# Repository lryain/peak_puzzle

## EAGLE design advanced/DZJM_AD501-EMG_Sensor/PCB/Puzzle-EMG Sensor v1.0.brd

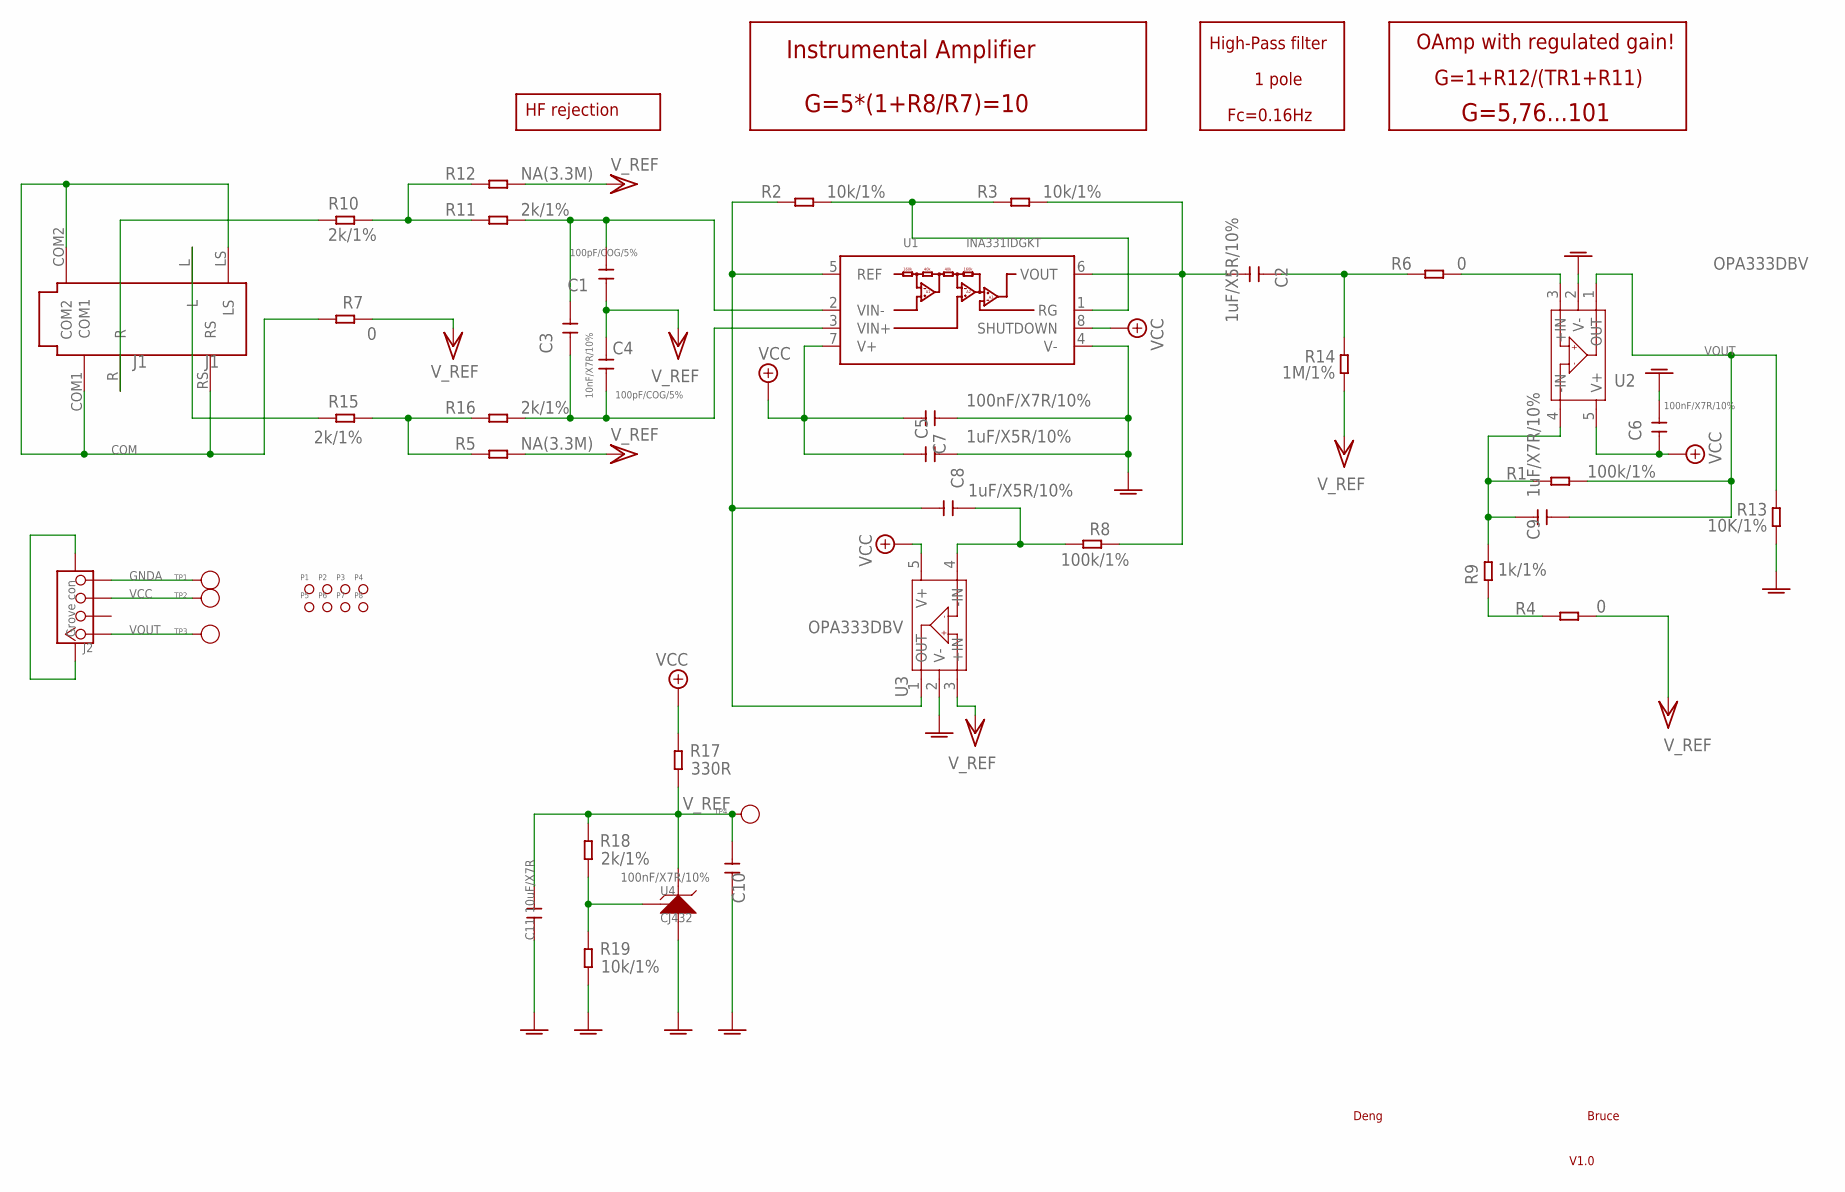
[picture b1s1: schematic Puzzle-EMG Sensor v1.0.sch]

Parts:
C1, C4: 100pF/COG/5%; C0603
C2, C7, C8: 1uF/X5R/10%; C0603
C3: 10nF/X7R/10%; C0603
C5, C6, C10: 100nF/X7R/10%; C0603
C9: 1uF/X7R/10%; C0603
C11: 10uF/X7R; C0805
J1: J1; 6P-SMD-3.5-NEW
J2: Grove con; 4P-SMD-2.0
P1, P2, P3, P4, P5, P6, P7, P8: PAD-MARK; ROUND-MARK-1.0
R1, R8: 100k/1%; R0603
R2, R3, R19: 10k/1%; R0603
R4, R6, R7: 0; R0603
R5, R12: NA(3.3M); R0603
R9: 1k/1%; R0603
R10, R11, R15, R16, R18: 2k/1%; R0603
R13: 10K/1%; R0603
R14: 1M/1%; R0603
R17: 330R; R0603
TP1: TP1; TP_4545
TP2: TP2; TP_4545
TP3: TP3; TP_4545
TP4: TP4; TP_4545
U1: INA331IDGKT; MSOP-8
U2, U3: OPA333DBV; SOT23-5
U4: CJ432; SOT23

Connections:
COM: J1.COM1, J1.COM2, J1.LS, J1.RS, R7.1
GNDA: C5.2, C6.1, C7.2, C10.2, C11.1, J2.4, R13.2, R19.1, TP1.T, U1.4 (V-), U2.2 (V-), U3.2 (V-), U4.3 (A)
unnamed: R4.1, R9.2
unnamed: C8.1, R8.1, U3.4 (-IN)
unnamed: J1.R, R10.1
unnamed: J1.L, R15.1
unnamed: R10.2, R11.2, R12.2
unnamed: R5.2, R15.2, R16.2
unnamed: C8.2, R2.2, U1.5 (REF), U3.1 (OUT)
unnamed: R2.1, R3.2, U1.1 (RG)
unnamed: C2.2, R6.2, R14.1
unnamed: R18.1, R19.2, U4.1 (R)
unnamed: C2.1, R3.1, R8.2, U1.6 (VOUT)
unnamed: C3.1, C4.1, R16.1, U1.3 (VIN+)
unnamed: C1.2, C3.2, R11.1, U1.2 (VIN-)
unnamed: R6.1, U2.3 (+IN)
unnamed: C9.1, R1.1, R9.1, U2.4 (-IN)
VCC: C5.1, C6.2, C7.1, J2.3, R17.2, TP2.T, U1.7 (V+), U1.8 (SHUTDOWN), U2.5 (V+), U3.5 (V+)
VOUT: C9.2, J2.1, R1.2, R13.1, TP3.T, U2.1 (OUT)
V_REF: C1.1, C4.2, C10.1, C11.2, J2.SS1, J2.SS2, R4.2, R5.1, R7.2, R12.1, R14.2, R17.1, R18.2, TP4.T, U3.3 (+IN), U4.2 (K)

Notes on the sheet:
G=1+R12/(TR1+R11)
G=5,76...101
Fc=0.16Hz
HF rejection
High-Pass filter
OAmp with regulated gain!
1 pole
G=5*(1+R8/R7)=10
Instrumental Amplifier
Deng
Bruce
V1.0

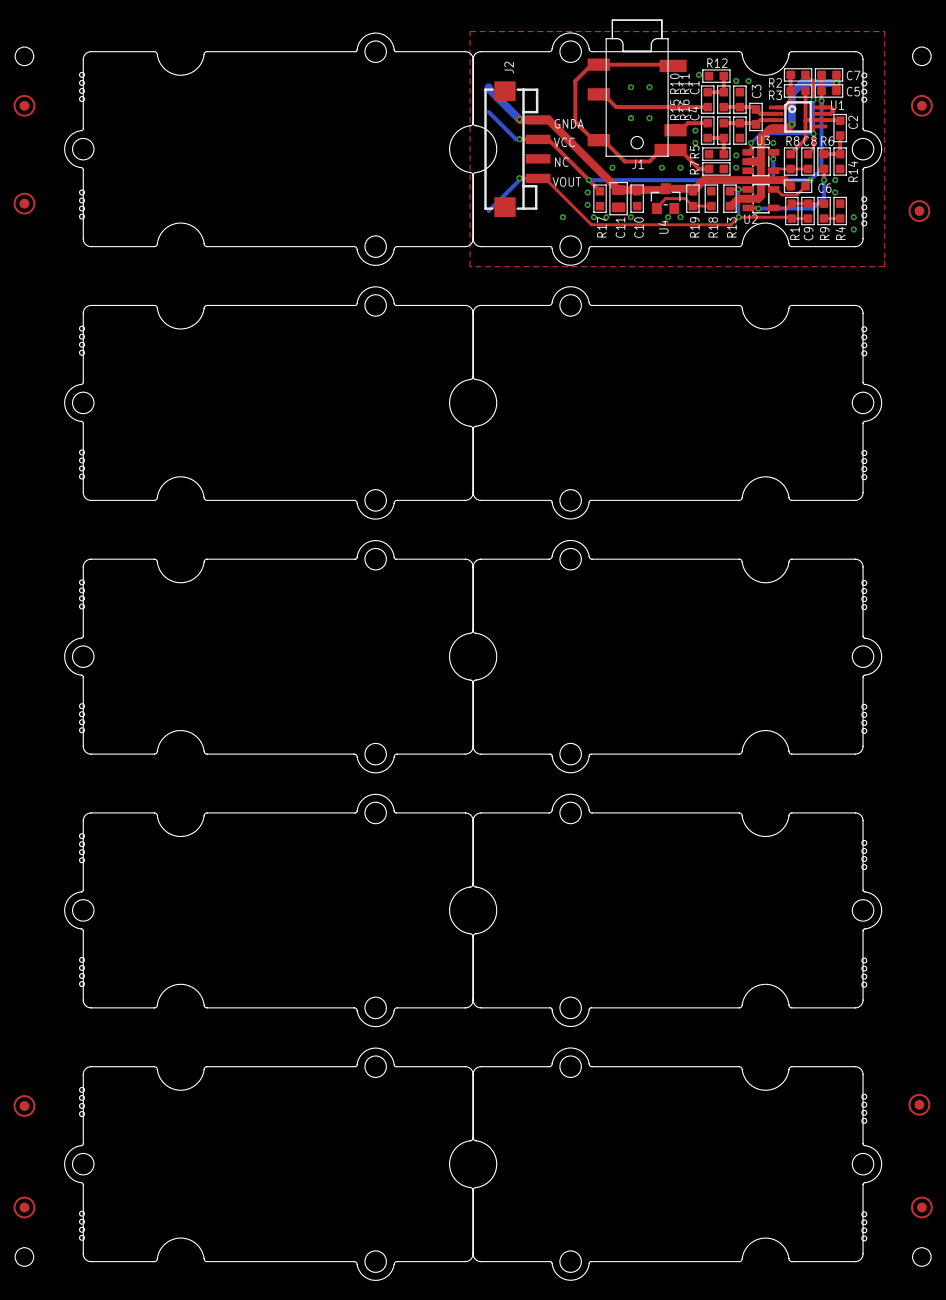
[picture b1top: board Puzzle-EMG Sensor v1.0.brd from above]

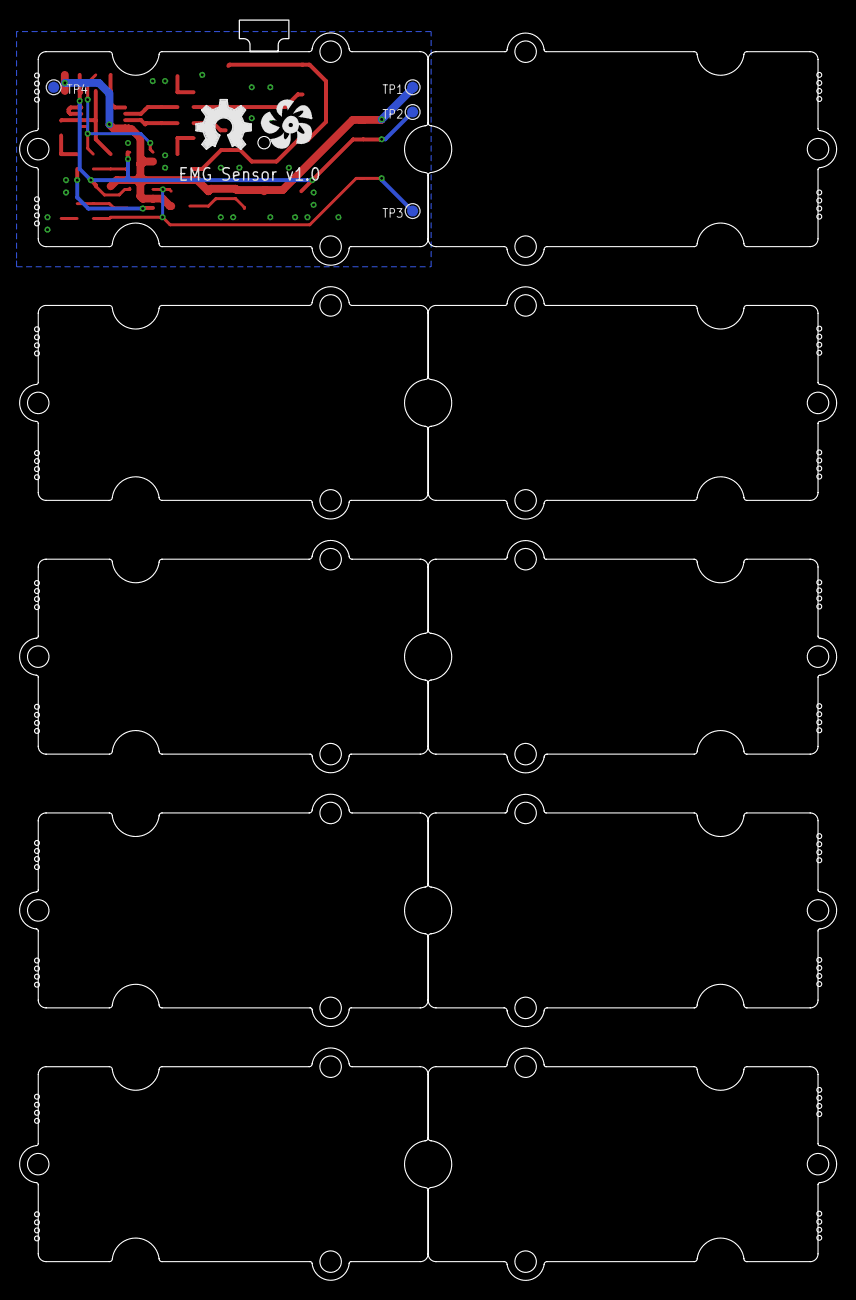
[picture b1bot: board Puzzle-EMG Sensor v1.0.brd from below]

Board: 2 copper layers, 83.7 x 129.3 mm, 60 parts (6 on the bottom side), 20 nets.

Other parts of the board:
U$2, U$5, U$6, U$7, U$8, U$9, U$10, U$11, U$12, U$13: GROVE-TEST-PLATFORM
U$3: OSHW_FILLX200_NOTEXT
U$14: DUINOFUN-LOGO-PCB-0.7

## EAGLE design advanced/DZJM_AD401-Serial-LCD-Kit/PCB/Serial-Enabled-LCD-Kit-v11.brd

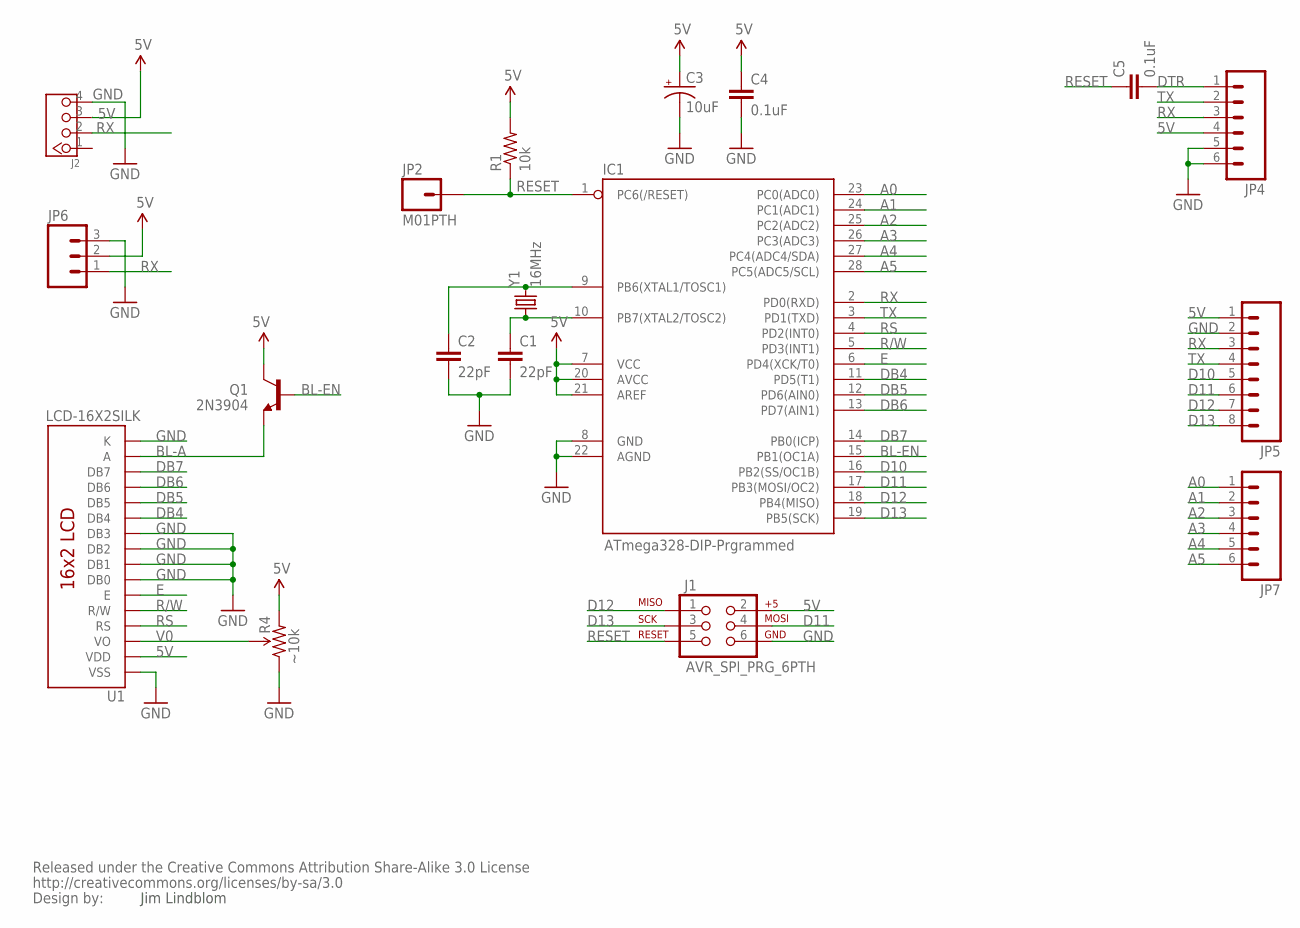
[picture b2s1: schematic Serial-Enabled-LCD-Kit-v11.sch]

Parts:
C1, C2: 22pF; CAP-PTH-SMALL2
C3: 10uF; CPOL-RADIAL-10UF-25V
C4, C5: 0.1uF; CAP-PTH-SMALL2
IC1: ATmega328-DIP-Prgrammed; DIL28-3
J1: AVR_SPI_PRG_6PTH; 2X3
J2: TWIG-4P-2.0'90D'; 4P-2.0-90D
JP2: M01PTH; 1X01
JP4, JP7: M06SIP; 1X06
JP5: M08; 1X08
JP6: M03PTH; 1X03
Q1: 2N3904; TO-92
R1: 10k; AXIAL-0.3
R4: ~10k; TRIM_POT_PTH
U1: LCD-16X2SILK; LCD-16X2
U$4: CREATIVE_COMMONS
Y1: 16MHz; HC49US

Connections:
5V: C3.1 (+), C4.1, IC1.7 (VCC), IC1.20 (AVCC), IC1.21 (AREF), J1.2, J2.3, JP4.4, JP5.1, JP6.2, Q1.3 (C), R1.P$2 (2), R4.3 (CW), U1.2 (VDD)
A0: IC1.23 (PC0(ADC0)), JP7.1
A1: IC1.24 (PC1(ADC1)), JP7.2
A2: IC1.25 (PC2(ADC2)), JP7.3
A3: IC1.26 (PC3(ADC3)), JP7.4
A4: IC1.27 (PC4(ADC4/SDA)), JP7.5
A5: IC1.28 (PC5(ADC5/SCL)), JP7.6
BL-A: Q1.1 (E), U1.15 (A)
BL-EN: IC1.15 (PB1(OC1A)), Q1.2 (B)
D10: IC1.16 (PB2(SS/OC1B)), JP5.5
D11: IC1.17 (PB3(MOSI/OC2)), J1.4, JP5.6
D12: IC1.18 (PB4(MISO)), J1.1, JP5.7
D13: IC1.19 (PB5(SCK)), J1.3, JP5.8
DB4: IC1.11 (PD5(T1)), U1.11 (DB4)
DB5: IC1.12 (PD6(AIN0)), U1.12 (DB5)
DB6: IC1.13 (PD7(AIN1)), U1.13 (DB6)
DB7: IC1.14 (PB0(ICP)), U1.14 (DB7)
DTR: C5.2, JP4.1
E: IC1.6 (PD4(XCK/T0)), U1.6 (E)
GND: C1.2, C2.2, C3.2 (-), C4.2, IC1.8 (GND), IC1.22 (AGND), J1.6, J2.4, JP4.5, JP4.6, JP5.2, JP6.3, R4.1 (CCW), U1.1 (VSS), U1.7 (DB0), U1.8 (DB1), U1.9 (DB2), U1.10 (DB3), U1.16 (K)
R/W: IC1.5 (PD3(INT1)), U1.5 (R/W)
RESET: C5.1, IC1.1 (PC6(/RESET)), J1.5, JP2.1, R1.P$1 (1)
RS: IC1.4 (PD2(INT0)), U1.4 (RS)
RX: IC1.2 (PD0(RXD)), J2.2, JP4.3, JP5.3, JP6.1
TX: IC1.3 (PD1(TXD)), JP4.2, JP5.4
V0: R4.2 (WIPER), U1.3 (VO)
XTAL1: C2.1, IC1.9 (PB6(XTAL1/TOSC1)), Y1.2
XTAL2: C1.1, IC1.10 (PB7(XTAL2/TOSC2)), Y1.1

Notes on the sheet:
Jim Lindblom

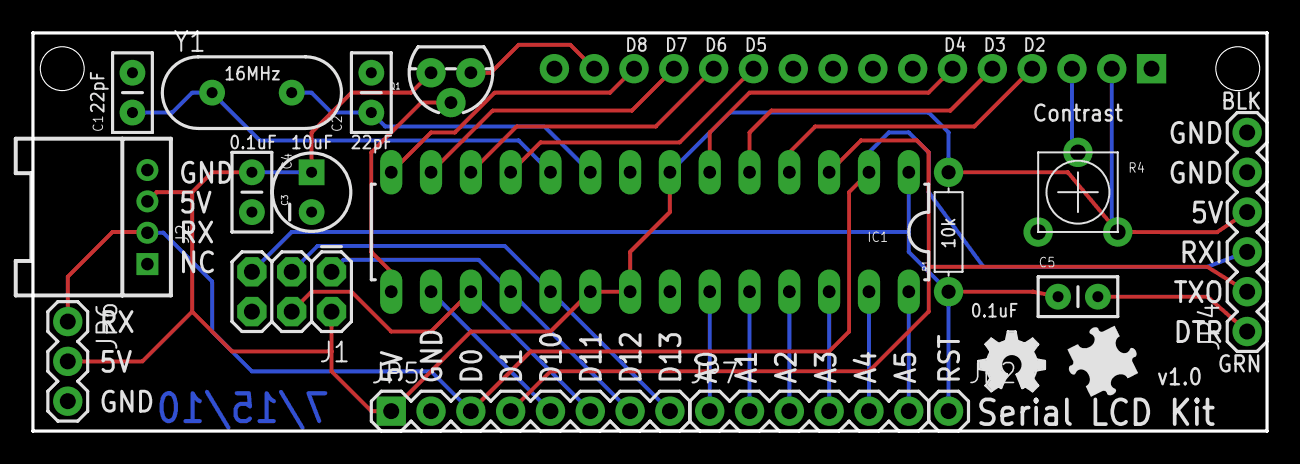
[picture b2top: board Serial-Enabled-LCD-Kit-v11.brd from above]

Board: 2 copper layers, 78.7 x 25.4 mm, 21 parts (1 on the bottom side), 28 nets.

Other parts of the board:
U$10: BRICK-LOGO-MIL-0.5
U$11: OPHW-LOGO-FILL-150

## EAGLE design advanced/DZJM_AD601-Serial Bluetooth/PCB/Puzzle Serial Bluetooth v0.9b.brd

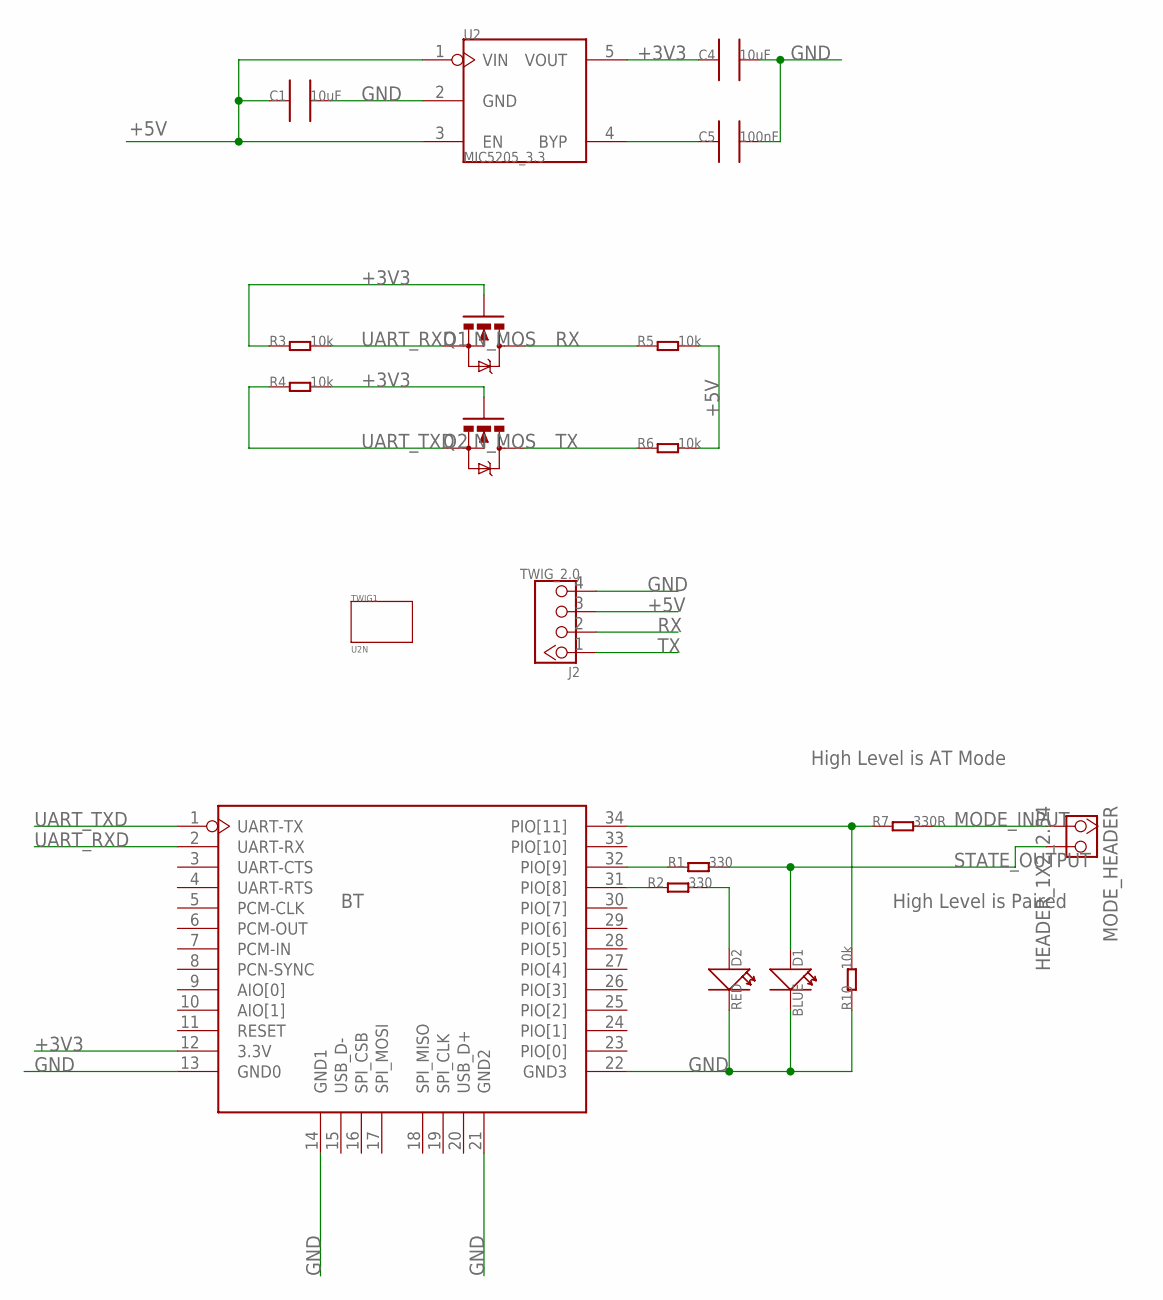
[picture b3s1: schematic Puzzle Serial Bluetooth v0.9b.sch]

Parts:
BT: SERIAL_BLUETEETHSMT; SERIAL_BLUETEETH
C1, C4: 10uF; 0805_S
C5: 100nF; 0603_S
D1: BLUE; LED0603
D2: RED; LED0603
J2: TWIG_2.0; 2.0_1X4
MODE_HEADER: HEADER_1X2_2.54; CK_1*2
Q1, Q2: N_MOS; SOT23
R1, R2: 330; 0603
R3, R4, R5, R6, R10: 10k; 0603_S
R7: 330R; 0603_S
TWIG1: U2N
U2: MIC5205_3.3; SOT23-5

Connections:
+3V3: BT.12 (3.3V), C4.1, Q1.1 (G), Q2.1 (G), R3.1, R4.2, U2.5 (VOUT)
+5V: C1.1, J2.3, R5.2, R6.2, U2.1 (VIN), U2.3 (EN)
GND: BT.13 (GND0), BT.14 (GND1), BT.21 (GND2), BT.22 (GND3), C1.2, C4.2, C5.2, D1.2 (-), D2.2 (-), J2.4, R10.1, U2.2 (GND)
MODE_INPUT: MODE_HEADER.1, R7.2
unnamed: D2.1 (+), R2.2
unnamed: C5.1, U2.4 (BYP)
unnamed: BT.34 (PIO[11]), R7.1, R10.2
unnamed: BT.31 (PIO[8]), R2.1
unnamed: BT.32 (PIO[9]), R1.1
RX: J2.2, Q1.3 (D), R5.1
STATE_OUTPUT: D1.1 (+), MODE_HEADER.2, R1.2
TX: J2.1, Q2.3 (D), R6.1
UART_RXD: BT.2 (UART-RX), Q1.2 (S), R3.2
UART_TXD: BT.1 (UART-TX), Q2.2 (S), R4.1

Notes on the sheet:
High Level is AT Mode
High Level is Paired

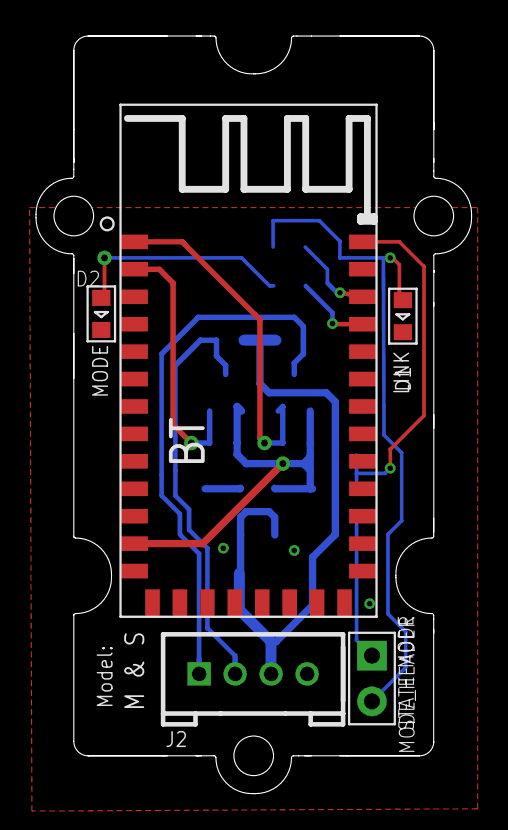
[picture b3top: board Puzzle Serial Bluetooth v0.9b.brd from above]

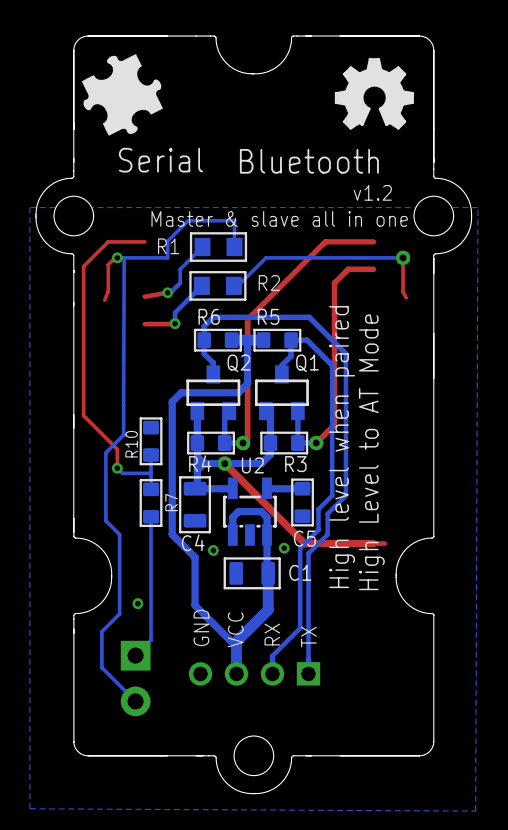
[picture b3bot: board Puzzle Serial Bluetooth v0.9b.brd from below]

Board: 2 copper layers, 24.2 x 42.1 mm, 22 parts (16 on the bottom side), 14 nets.

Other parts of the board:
U$1: BRICK-LOGO-MIL-0.5
U$2: OPHW-LOGO-FILL-150

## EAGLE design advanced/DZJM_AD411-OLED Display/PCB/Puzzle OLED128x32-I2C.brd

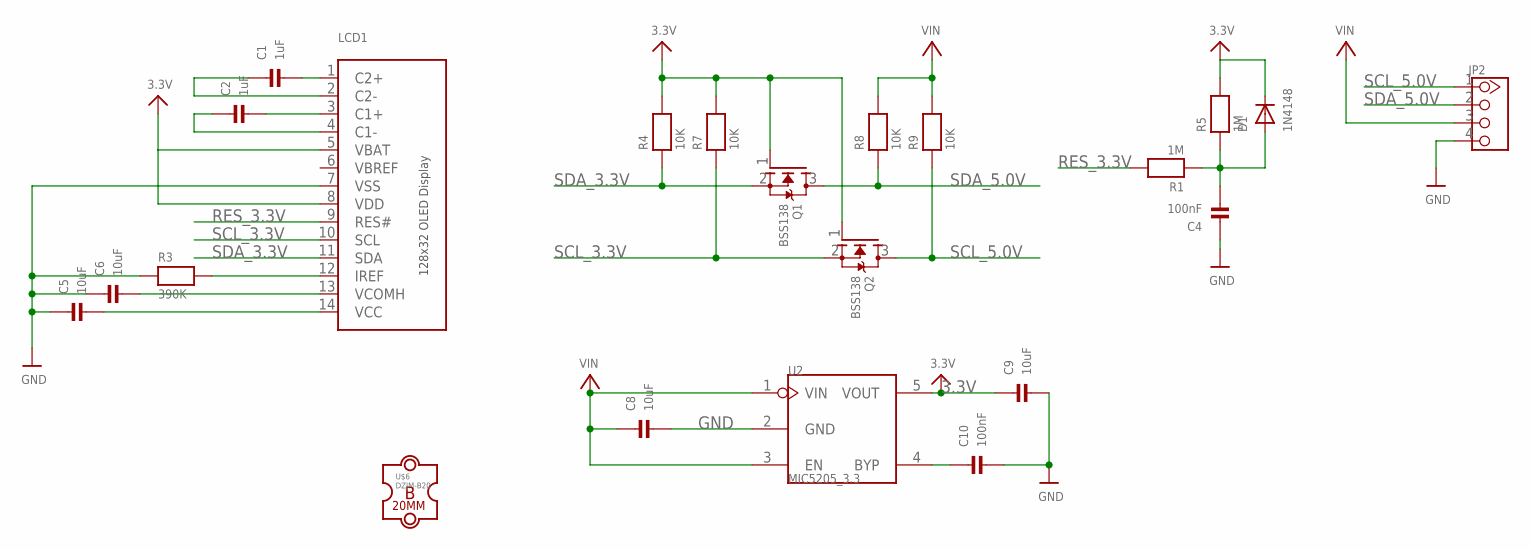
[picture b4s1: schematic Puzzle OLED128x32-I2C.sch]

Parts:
C1, C2: 1uF; 0603
C4, C10: 100nF; 0603
C5, C6, C8, C9: 10uF; 0805
D1: 1N4148; SOD-323F
JP2: M048; 4P-SMD-2.0-90D
LCD1: DISP_OLED_UG-2832HSWEG02; UG-2832HSWEG02_WRAPUNDER
Q1, Q2: BSS138; SOT23-WIDE
R1: 1M; 0603
R3: 390K; 0603
R4, R7, R8, R9: 10K; 0805
R5: 1M; 0805
U2: MIC5205_3.3; SOT23-5
U$6: DZJM-B20; DZJM-B20-2P-B

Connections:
3.3V: C9.1, D1.C, LCD1.5 (VBAT), LCD1.8 (VDD), Q1.1 (G), Q2.1 (G), R4.2, R5.2, R7.2, U2.5 (VOUT)
GND: C4.1, C5.1, C6.1, C8.2, C9.2, C10.2, JP2.4, LCD1.7 (VSS), R3.1, U2.2 (GND)
unnamed: C1.2, LCD1.1 (C2+)
unnamed: C1.1, LCD1.2 (C2-)
unnamed: C2.2, LCD1.3 (C1+)
unnamed: C2.1, LCD1.4 (C1-)
unnamed: C6.2, LCD1.13 (VCOMH)
unnamed: C5.2, LCD1.14 (VCC)
unnamed: LCD1.12 (IREF), R3.2
unnamed: C10.1, U2.4 (BYP)
unnamed: C4.2, D1.A, R1.1, R5.1
RES_3.3V: LCD1.9 (RES#), R1.2
SCL_3.3V: LCD1.10 (SCL), Q2.2 (S), R7.1
SCL_5.0V: JP2.1, Q2.3 (D), R9.1
SDA_3.3V: LCD1.11 (SDA), Q1.2 (S), R4.1
SDA_5.0V: JP2.2, Q1.3 (D), R8.1
VBREF: LCD1.6 (VBREF)
VIN: C8.1, JP2.3, R8.2, R9.2, U2.1 (VIN), U2.3 (EN)

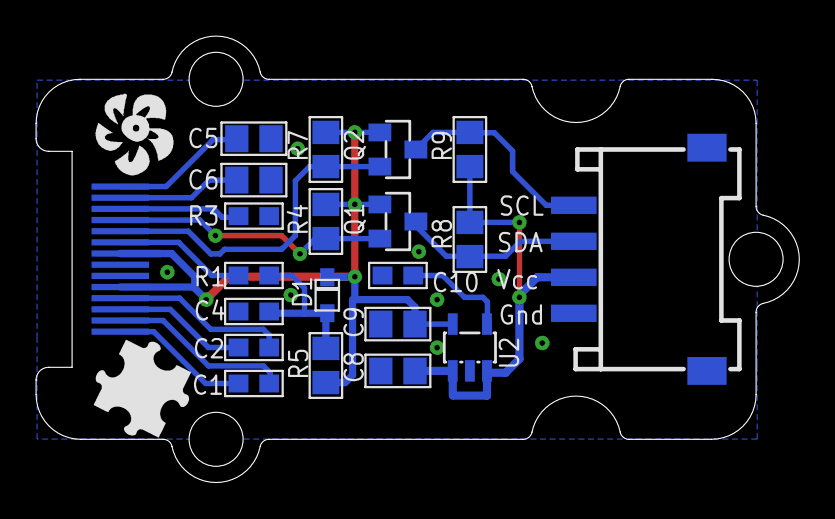
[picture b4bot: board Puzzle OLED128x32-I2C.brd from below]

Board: 2 copper layers, 42.4 x 24.8 mm, 24 parts (21 on the bottom side), 17 nets.

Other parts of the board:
U$4: DUINOFUN-LOGO-PCB-0.6
U$7: BRICK-LOGO-2-B-MIL-0.6

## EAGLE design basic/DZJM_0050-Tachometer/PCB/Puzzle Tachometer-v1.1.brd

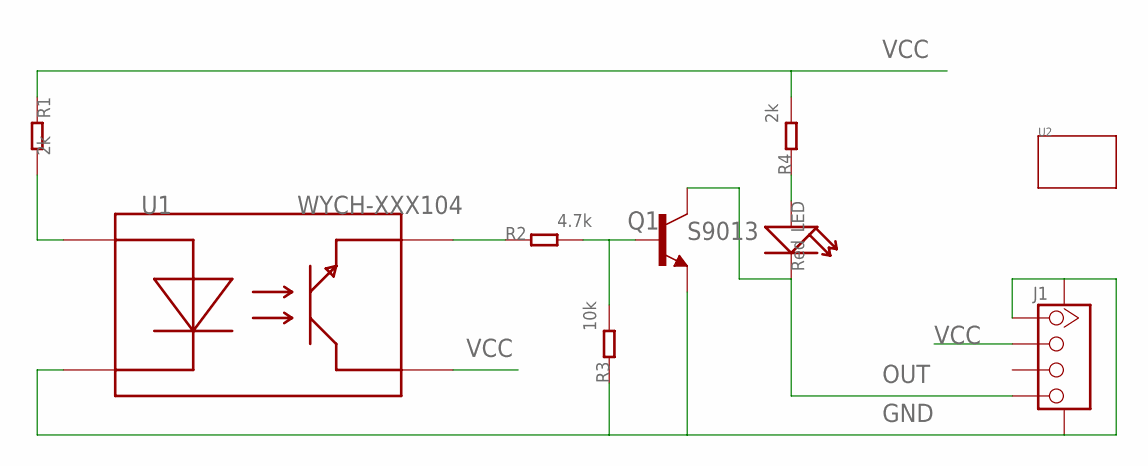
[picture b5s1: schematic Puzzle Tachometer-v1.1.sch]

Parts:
J1: TWIG-4P-2.0-SMD-FEMALE-REINFORCE'DD'; 4P-SMD-2.0
LED: Red; LED-0603
Q1: S9013; SOT23-3
R1, R4: 2k; R0603
R2: 4.7k; R0603
R3: 10k; R0603
U1: WYCH-XXX104; WYCH104
U2: TWIG-2U; 2U-DIM-W/-DRILL

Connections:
GND: J1.1, J1.SS1, J1.SS2, Q1.2 (E), R3.1, U1.2
unnamed: R1.2, U1.1
unnamed: Q1.1 (B), R2.2, R3.2
unnamed: R2.1, U1.4
unnamed: LED.+, R4.1
OUT: J1.4, LED.-, Q1.3 (C)
VCC: J1.2, R1.1, R4.2, U1.3

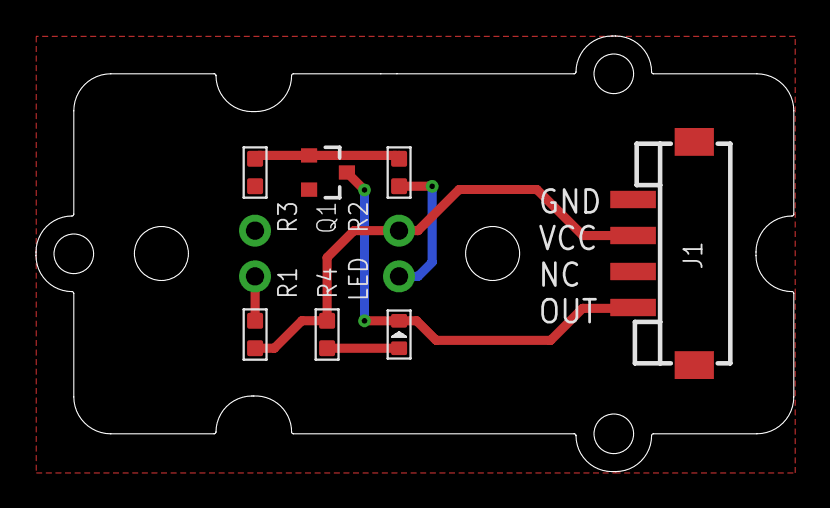
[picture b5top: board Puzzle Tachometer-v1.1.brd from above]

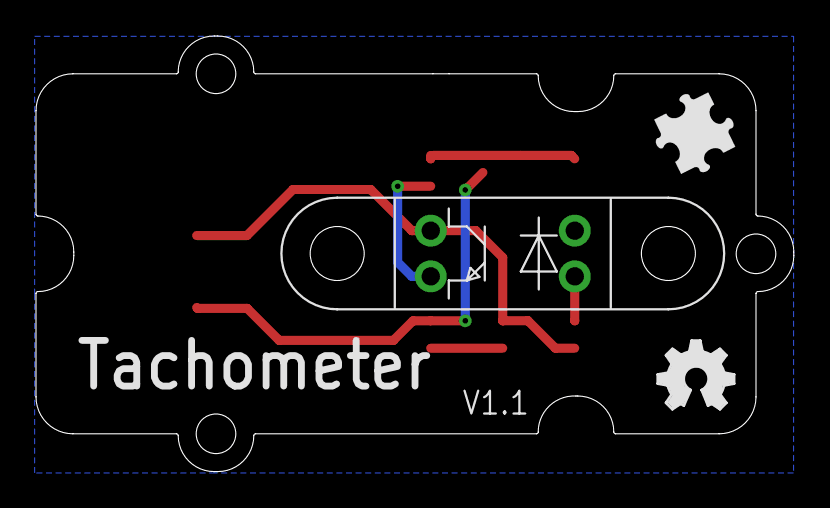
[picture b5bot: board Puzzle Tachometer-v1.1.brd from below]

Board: 2 copper layers, 42.1 x 24.2 mm, 11 parts (3 on the bottom side), 7 nets.

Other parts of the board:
U$3: OSHW_FILLX150_NOTEXT
U$4: BRICK-LOGO-MIL-0.5

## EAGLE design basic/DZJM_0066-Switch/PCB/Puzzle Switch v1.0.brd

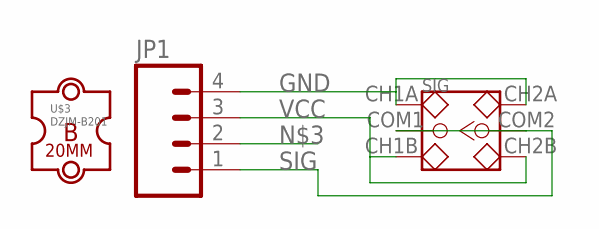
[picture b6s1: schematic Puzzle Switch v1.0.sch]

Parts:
JP1: M04POLAR; JMZY-1X4
SIG: SWITCH-2CH-6P; 6P-2CH-2.54-7.6X3.0
U$3: DZJM-B201; DZJM-B20-1P

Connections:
GND: JP1.4, SIG.CH1A, SIG.CH2A
SIG: JP1.1, SIG.COM1, SIG.COM2
VCC: JP1.3, SIG.CH1B, SIG.CH2B

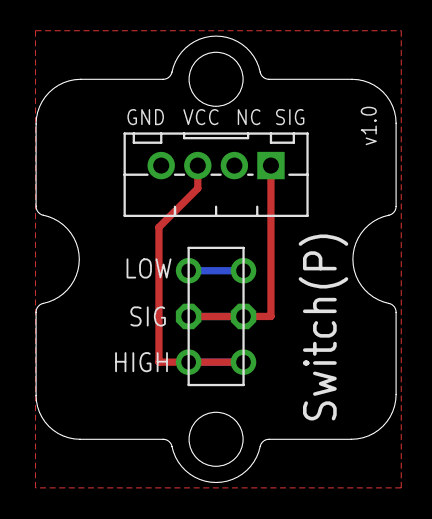
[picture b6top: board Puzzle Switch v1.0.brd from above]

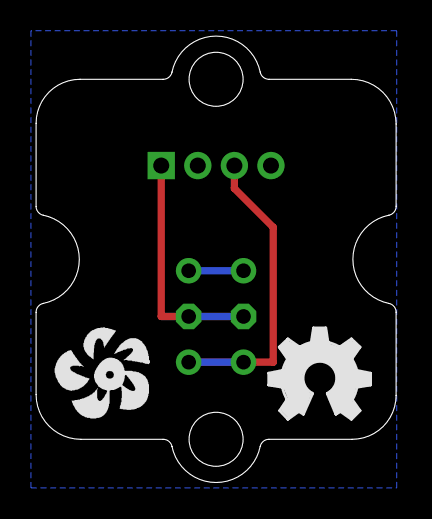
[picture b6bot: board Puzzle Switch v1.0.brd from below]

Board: 2 copper layers, 20.0 x 24.8 mm, 5 parts (2 on the bottom side), 3 nets.

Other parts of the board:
U$2: OSHW_FILLX200_NOTEXT
U$4: DUINOFUN-LOGO-PCB-0.7

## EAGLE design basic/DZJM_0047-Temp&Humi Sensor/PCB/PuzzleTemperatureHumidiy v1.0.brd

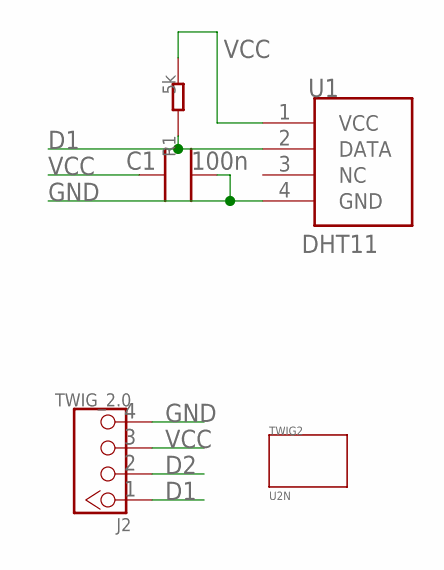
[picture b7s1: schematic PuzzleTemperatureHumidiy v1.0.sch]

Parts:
C1: 100n; 0603
J2: TWIG_2.0; 2.0_1X4
R1: 5k; 0603
TWIG2: U2N
U1: DHT11

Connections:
D1: J2.1, R1.1, U1.2 (DATA)
D2: J2.2
GND: C1.2, J2.4, U1.4 (GND)
VCC: C1.1, J2.3, R1.2, U1.1 (VCC)

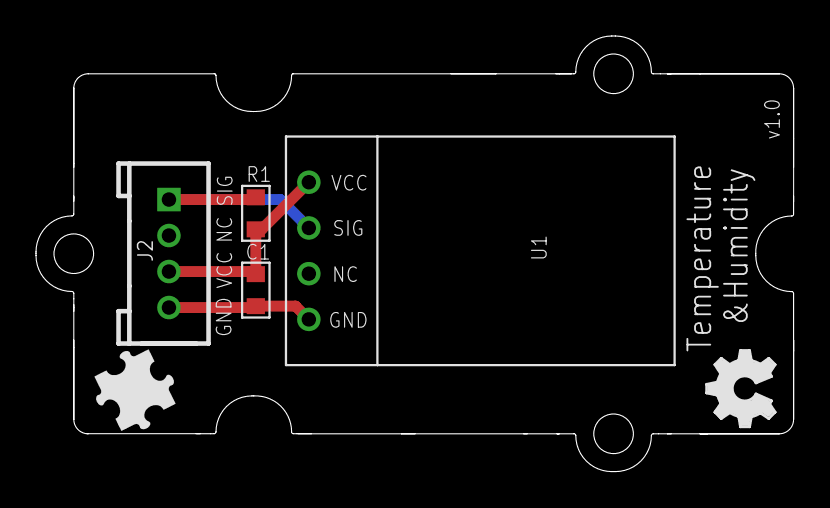
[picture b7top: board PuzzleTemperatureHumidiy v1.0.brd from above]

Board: 2 copper layers, 42.1 x 24.2 mm, 7 parts (0 on the bottom side), 3 nets.

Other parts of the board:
U$1: OPHW-LOGO-FILL-150
U$2: BRICK-LOGO-MIL-0.5

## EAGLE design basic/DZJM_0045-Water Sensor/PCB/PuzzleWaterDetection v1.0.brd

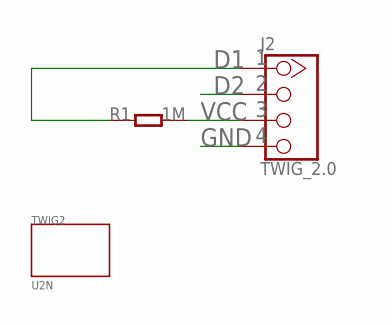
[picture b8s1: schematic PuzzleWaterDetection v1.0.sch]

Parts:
J2: TWIG_2.0; 2.0_1X4
R1: 1M; 0603
TWIG2: U2N

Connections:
D1: J2.1, R1.1
D2: J2.2
GND: J2.4
VCC: J2.3, R1.2

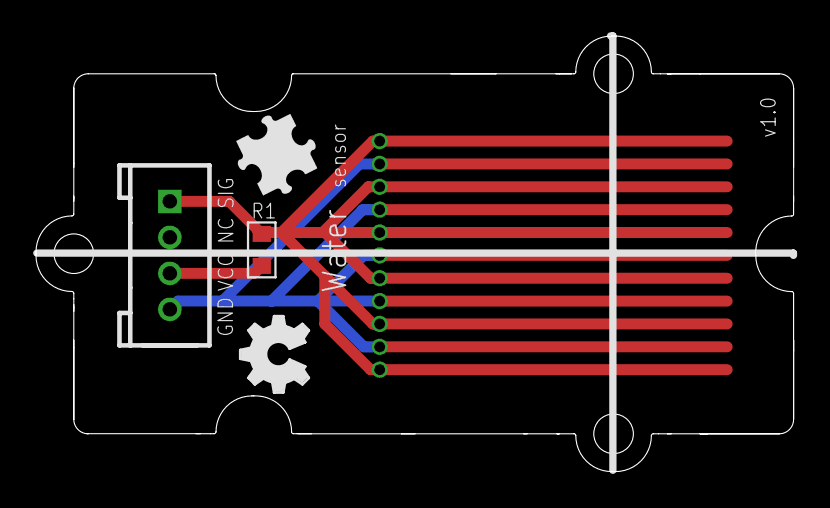
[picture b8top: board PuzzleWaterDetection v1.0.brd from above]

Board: 2 copper layers, 42.1 x 24.2 mm, 5 parts (0 on the bottom side), 2 nets.

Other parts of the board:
U$1: BRICK-LOGO-MIL-0.5
U$2: OSHW_FILLX150_NOTEXT

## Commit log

2016-12-17 DZJM_0001-Button
2016-12-17 DZJM_0002-Buzzer
2016-12-17 DZJM_0003-LED
2016-12-17 DZJM_0004-Rotary
2016-12-17 DZJM_0005-Slide Potentiometer
2016-12-17 DZJM_0006-4-Digit Display
2016-12-17 DZJM_0007-Chainable RGB LED
2016-12-17 DZJM_0008-Circular LED
2016-12-17 DZJM_0009-Collision Sensor
2016-12-17 DZJM_0010-Digital Light Sensor
2016-12-17 DZJM_0011-Encoder
2016-12-17 DZJM_0012_MQx Gas Sensor
2016-12-17 DZJM_0013-GPS
2016-12-17 DZJM_0014-Hall Sensor
2016-12-17 DZJM_0015-I2C Color Sensor
2016-12-17 DZJM_0016-I2C Hub
2016-12-17 DZJM_0018-IMU_9DOF
2016-12-17 Infrared Emitter and Receiver
2016-12-17 DZJM_0021-Infrared Reflective Sensor
2016-12-17 puzzle initial commit
2016-12-17 DZJM_0031-Relay
2016-12-17 DZJM_0032-RTC
2016-12-17 DZJM_0033-Screw Terminal
2016-12-17 DZJM_0040-Temperature_Sensor(Analog)
2016-12-17 Thumb Joystick and Vibration Motor
2016-12-17 DZJM_0038-Sound Sensor
2016-12-17 DZJM_0045-Water Sensor
2016-12-17 DZJM_0047-Temp&Humi Sensor
2016-12-17 DZJM_0066-Switch
2016-12-17 DZJM_0064-Protoshield
2016-12-17 DZJM_0050-Tachometer
2016-12-17 advanced initial commit

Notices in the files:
parts and their libraries:
SparkFun: Released under the Creative Commons Attribution Share-Alike 3.0 License
SparkFun: http://creativecommons.org/licenses/by-sa/3.0
SparkFun: Licensing: CC v3.0 Share-Alike You are welcome to use this library for commercial purposes.
